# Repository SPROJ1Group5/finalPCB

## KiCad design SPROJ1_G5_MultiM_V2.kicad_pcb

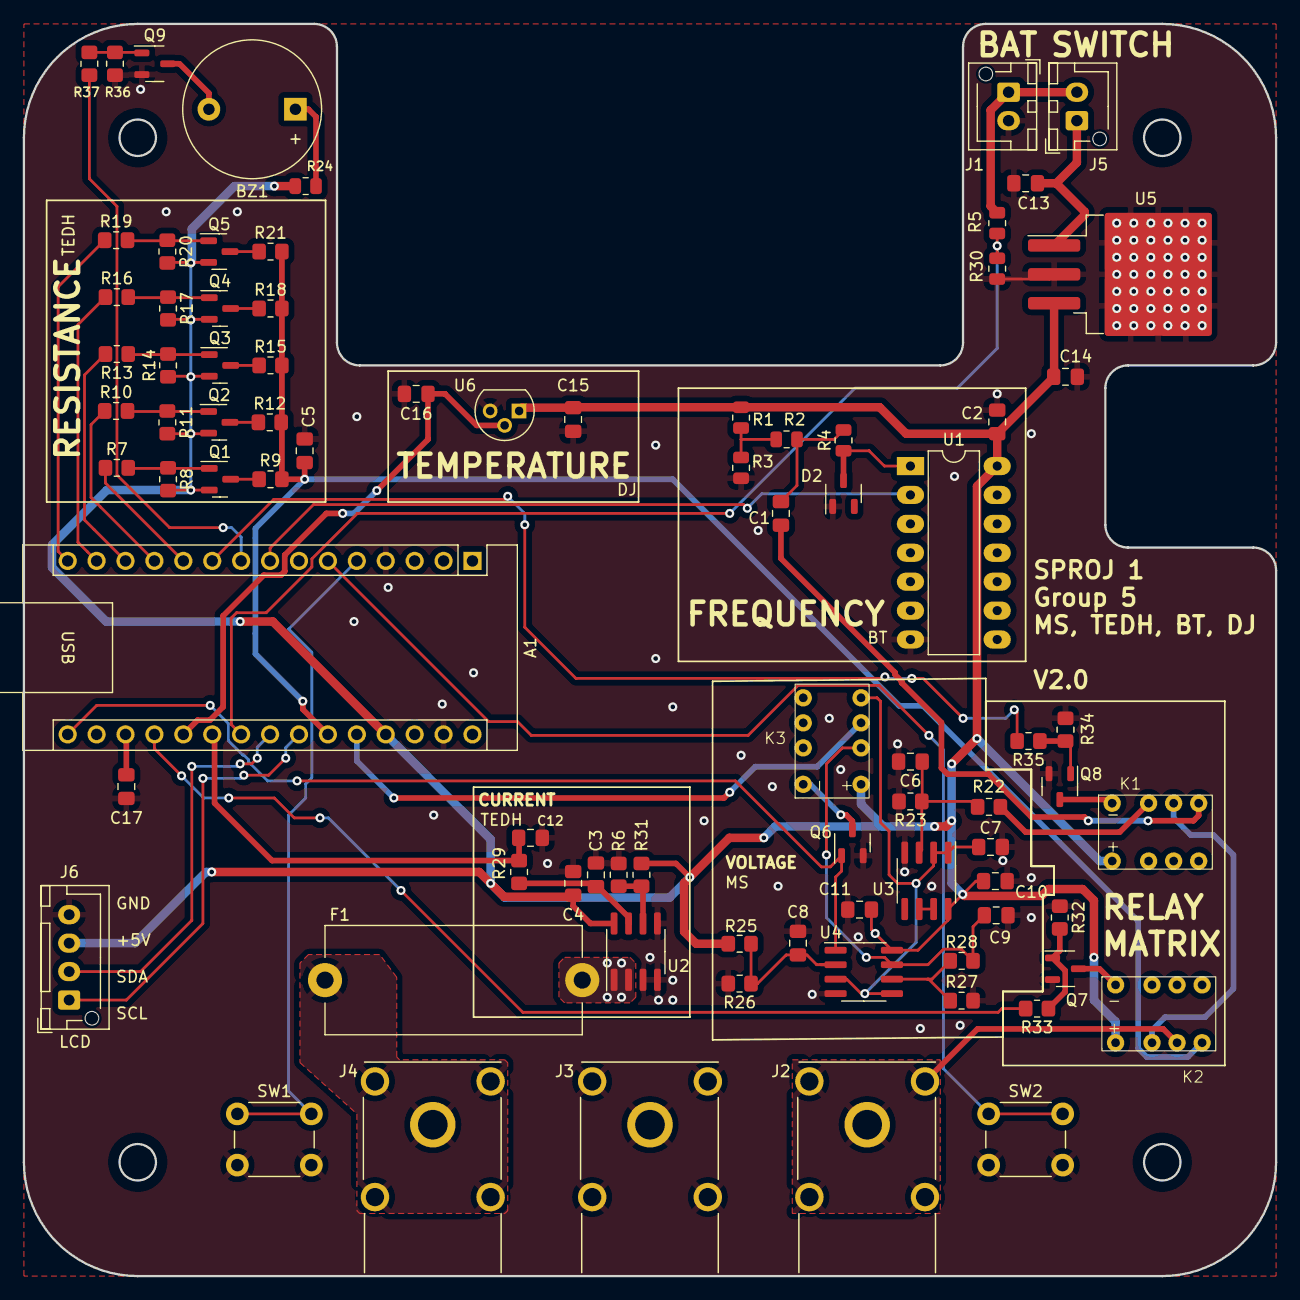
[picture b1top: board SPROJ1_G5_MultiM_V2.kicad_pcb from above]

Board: 2 copper layers, 110.0 x 110.0 mm, 84 parts (0 on the bottom side), 59 nets.

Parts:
A1: Arduino_Nano_v3.x; Arduino_Nano
BZ1: Buzzer; Buzzer_12x9.5RM7.6
C1, C4, C5, C15: 100n; C_0805_2012Metric_Pad1.18x1.45mm_HandSolder
C2: 330n; C_0805_2012Metric_Pad1.18x1.45mm_HandSolder
C3: 1n; C_0805_2012Metric_Pad1.18x1.45mm_HandSolder
C6, C7, C8, C9, C14, C17: 10u; C_0805_2012Metric_Pad1.18x1.45mm_HandSolder
C10, C11: 10uF; C_0805_2012Metric_Pad1.18x1.45mm_HandSolder
C12: 6.8n; C_0805_2012Metric_Pad1.18x1.45mm_HandSolder
C13: 220n; C_0805_2012Metric_Pad1.18x1.45mm_HandSolder
C16: 10n; C_0805_2012Metric_Pad1.18x1.45mm_HandSolder
D2: Zener 5V; SOT-23-3
F1: Fuse; Fuseholder_Cylinder-5x20mm_Stelvio-Kontek_PTF78_Horizontal_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
J1: 9V Battery; JST_XH_B2B-XH-AM_1x02_P2.50mm_Vertical
J2, J3, J4: FCR7350R; FCR7350
J5: Switch; JST_XH_B2B-XH-AM_1x02_P2.50mm_Vertical
J6: Conn_01x04_Pin; JST_XH_B4B-XH-AM_1x04_P2.50mm_Vertical
K1, K2, K3: HFD4/005; HFD4
Q1, Q2, Q3, Q4, Q5: IRLML6401; SOT-23
Q6, Q7, Q8, Q9: NMOS; SOT-23-3
R1, R3, R4: 15K; R_0805_2012Metric
R2: 50; R_0805_2012Metric
R5, R30: 100k; R_0805_2012Metric
R6: 0R; R_0805_2012Metric_Pad1.20x1.40mm_HandSolder
R7, R10, R13, R16, R19, R33, R35, R37: 150; R_0805_2012Metric_Pad1.20x1.40mm_HandSolder
R8, R11, R14, R15, R17, R20, R32, R34, R36: 10k; R_0805_2012Metric_Pad1.20x1.40mm_HandSolder
R9: 100; R_0805_2012Metric_Pad1.20x1.40mm_HandSolder
R12: 1k; R_0805_2012Metric_Pad1.20x1.40mm_HandSolder
R18: 100k; R_0805_2012Metric_Pad1.20x1.40mm_HandSolder
R21: 1M; R_0805_2012Metric_Pad1.20x1.40mm_HandSolder
R22, R26: 15K; R_0805_2012Metric_Pad1.20x1.40mm_HandSolder
R23, R25: 5K; R_0805_2012Metric_Pad1.20x1.40mm_HandSolder
R24: 100R; R_0805_2012Metric
R27: 10K; R_0805_2012Metric_Pad1.20x1.40mm_HandSolder
R28: 30K; R_0805_2012Metric_Pad1.20x1.40mm_HandSolder
R29, R31: 4K7; R_0805_2012Metric_Pad1.20x1.40mm_HandSolder
SW1, SW2: SW_Omron_B3FS; SW_PUSH_6mm
U1: 7414; DIP-14_W7.62mm_LongPads
U2: ACS723xLCTR-05AB; SOIC-8_3.9x4.9mm_P1.27mm
U3, U4: LMV358; SOIC-8_3.9x4.9mm_P1.27mm
U5: L7805; TO-263-3_TabPin2
U6: LM35-DZ; TO-92

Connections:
+5V: A1.27 (+5V), C2.1, C4.1, C10.1, C11.1, C14.1, C15.1, J6.3, K1.1 (+), K2.1 (+), K3.1 (+), Q1.2 (S), Q2.2 (S), Q3.2 (S), Q4.2 (S), Q5.2 (S), R1.1, R8.2, R11.2, R14.1, R17.2, R20.2, R24.1, R25.1, R31.1, U1.14 (VCC), U2.8 (VCC), U3.8 (V+), U4.8 (V+), U5.3 (OUT), U6.1 (+VS)
+9V: J1.1, J5.2, R5.1
A: F1.1, J4.P$1, J4.P$2, J4.P$3, J4.P$4, J4.P$5
BATTERY VOLTAGE: A1.22 (A3), R5.2, R30.1
Buzzer: A1.9 (D6), R37.1
COM: A1.4 (GND), A1.29 (GND), C2.2, C3.2, C4.2, C5.2, C6.2, C7.2, C8.2, C9.2, C10.2, C11.2, C12.2, C13.2, C14.2, C15.2, C16.2, C17.2, D2.1 (A), J1.2, J3.P$1, J3.P$2, J3.P$3, J3.P$4, J3.P$5, J6.4, Q6.2 (S), Q7.2 (S), Q8.2 (S), Q9.2 (S), R3.2, R6.2, R23.2, R26.2, R27.2, R30.2, R32.1, R34.1, R36.2, SW1.2, SW2.2, U1.7 (GND), U2.3 (IP-), U2.4 (IP-), U2.5 (GND), U3.4 (V-), U4.4 (V-), U5.2 (GND), U6.3 (GND)
CURRENT: A1.21 (A2), C12.1, R29.2
D5: A1.8 (D5), U1.2
D8: A1.11 (D8), R7.1
D9: A1.12 (D9), R10.1
D10: A1.13 (D10), R13.2
D11: A1.14 (D11), R16.1
D12: A1.15 (D12), R19.1
FREQUENCY IN: C1.1, K1.5
HighRange: C7.1, K3.4, U3.1, U3.2 (-), U4.3 (+), U4.5 (+)
LowRange: C9.1, K3.2, R28.2, U4.7
NEXT: A1.6 (D3), SW2.1
unnamed: A1.18 (AREF), C17.1
unnamed: BZ1.2 (+), Q9.3 (D)
unnamed: BZ1.1 (-), R24.2
unnamed: C1.2, R2.2, R4.2
unnamed: D2.3 (K), R4.1, U1.1
unnamed: F1.2, U2.1 (IP+), U2.2 (IP+)
unnamed: C13.1, J5.1, U5.1 (IN)
unnamed: K1.8 (-), Q8.3 (D)
unnamed: K1.6, K2.2
unnamed: K2.8 (-), Q7.3 (D)
unnamed: K3.8 (-), Q6.3 (D)
unnamed: Q1.3 (D), R9.1
unnamed: Q1.1 (G), R7.2, R8.1
unnamed: Q2.3 (D), R12.1
unnamed: Q2.1 (G), R10.2, R11.1
unnamed: Q3.3 (D), R15.1
unnamed: Q3.1 (G), R13.1, R14.2
unnamed: Q4.3 (D), R18.1
unnamed: Q4.1 (G), R16.2, R17.1
unnamed: Q5.3 (D), R21.1
unnamed: Q5.1 (G), R19.2, R20.1
unnamed: Q7.1 (G), R32.2, R33.1
unnamed: Q8.1 (G), R34.2, R35.1
unnamed: Q9.1 (G), R36.1, R37.2
unnamed: R1.2, R2.1, R3.1
unnamed: R6.1, R31.2, U2.6 (BW_SEL)
unnamed: C3.1, R29.1, U2.7 (VIOUT)
unnamed: C6.1, R22.2, R23.1, U3.3 (+)
unnamed: U3.6 (-), U3.7
unnamed: C8.1, R25.2, R26.1, U4.2 (-)
unnamed: R27.1, R28.1, U4.6 (-)
PREVIOUS: A1.5 (D2), SW1.1
RESISTANCE: A1.25 (A6), C5.1, K2.4, R9.2, R12.2, R15.2, R18.2, R21.2
RangeSel: A1.16 (D13), Q6.1 (G), U4.1
Relay1: A1.19 (A0), R33.2
Relay2: A1.10 (D7), R35.2
SCL: A1.24 (A5), J6.1
SDA: A1.23 (A4), J6.2
TEMPERATURE: A1.20 (A1), C16.1, U6.2 (Vout)
VOLTAGE: A1.26 (A7), K3.3
VOLTAGE IN: K1.7, R22.1
VRf: J2.P$1, J2.P$2, J2.P$3, J2.P$4, J2.P$5, K2.3

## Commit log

2023-11-16 Some routing done. There is still more schematic work to be done....
2023-11-16 Small update
    Some files got changed after closing kicad.
2023-11-16 V0.1 Done
    The first full routing is complete. There is no LM35 sensor included.
    PS.
    The silkscreen art can be removed, but please no;)
2023-11-16 Fixed minor issues
    - Moved the relay further away from the current sensor.
    - Added vias near the ground connection of the current sensort
    - Swapped 3D models for the correct ones
    - Moved ground plane away from the mounting holes
    - Fixed pin capability related issue
2023-11-17 V1.0 Complete
2023-12-15 Made the schematic more readable.
    Made the schematic more readable.
2023-12-15 Added the files
